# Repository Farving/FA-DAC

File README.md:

# FA-DAC
Farving Acoustic DAC /w FA-Core interface

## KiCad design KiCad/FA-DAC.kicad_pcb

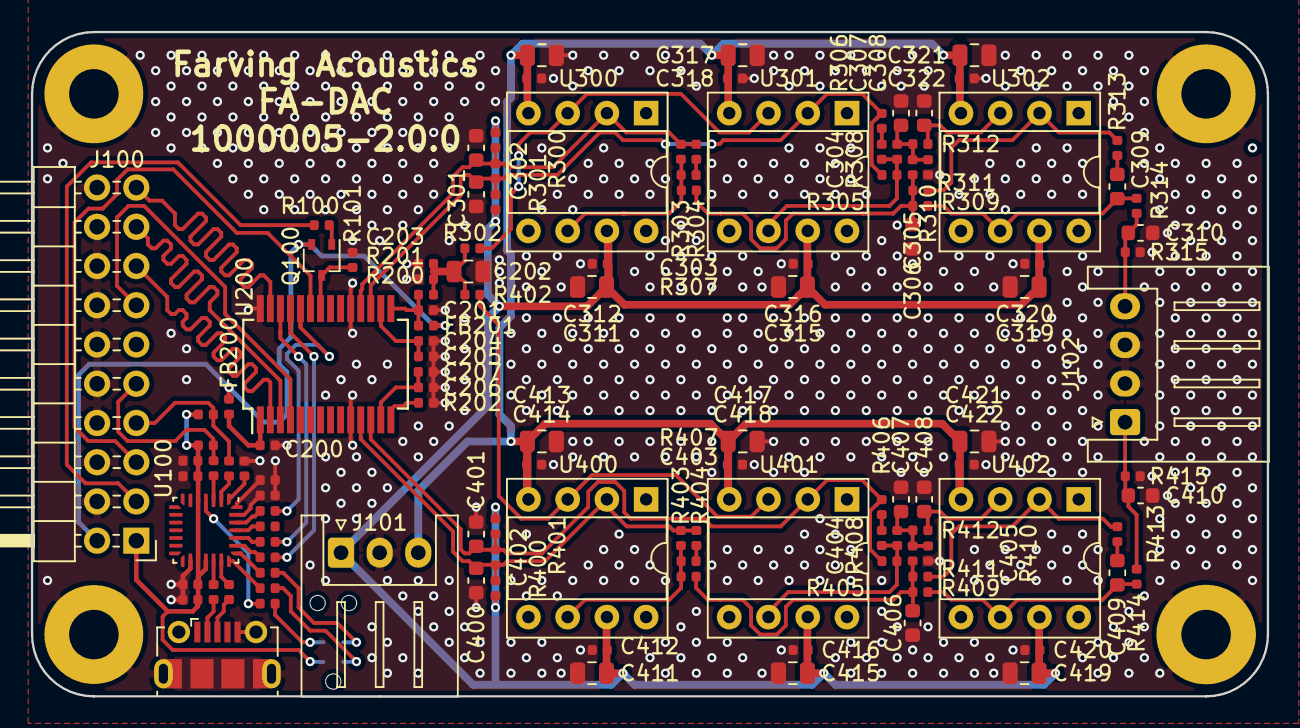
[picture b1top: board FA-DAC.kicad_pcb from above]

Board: 2 copper layers, 80.0 x 43.0 mm, 128 parts (1 on the bottom side), 71 nets.

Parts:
C1: 4.7u; C_0402_1005Metric
C2, C200, C201, C203, C204, C206, C302, C312, C314, C316, C318, C320, C322, C402, C412, C414, C416, C418, C420, C422: 100n; C_0402_1005Metric
C3: 10n; C_0402_1005Metric
C4: 1u; C_0402_1005Metric
C202: 47u; C_0805_2012Metric
C205, C207: 10u; C_0402_1005Metric
C300, C301, C400, C401: 1n; C_0603_1608Metric
C303, C304, C403, C404: 100p; C_0402_1005Metric
C305, C405: 390p; C_0402_1005Metric
C306, C307, C406, C407: 5.6n; C_0603_1608Metric
C308, C309, C408, C409: 2.7n; C_0603_1608Metric
C310, C410: 3.9n; C_0603_1608Metric
C311, C313, C315, C317, C319, C321, C411, C413, C415, C417, C419, C421: 10u; C_0805_2012Metric
FB200, FB201: 600Z; L_0402_1005Metric
J100: Conn_02x10_Odd_Even; PinHeader_2x10_P2.54mm_Horizontal
J101: JST_XH_S3B; JST_XH_S3B-XH-A_1x03_P2.50mm_Horizontal
J102: JST_XH_S4B; JST_XH_S4B-XH-A_1x04_P2.50mm_Horizontal
J103: USB_OTG; USB_Micro-B_Molex-105017-0001
J104: TC2030; Tag-Connect_TC2030-IDC-NL_2x03_P1.27mm_Vertical
PCB100: 70x43; PCB_Board_70x43
Q100: BC856W; SOT-323_SC-70
R1, R2: 2.2k; R_0402_1005Metric
R3, R4, R5, R6, R7, R8, R12, R13, R14, R304, R306, R313, R404, R406, R413: 100R; R_0402_1005Metric
R9, R100, R101: 10k; R_0402_1005Metric
R10, R11, R17, R18: 0R; R_0402_1005Metric
R200: 2.21k; R_0402_1005Metric
R201: 2.8k; R_0402_1005Metric
R202: 2.49k; R_0402_1005Metric
R300, R301, R303, R305, R400, R401, R403, R405: 2k; R_0402_1005Metric
R302, R307, R308, R402, R407, R408: 680R; R_0402_1005Metric
R309, R310, R409, R410: 220R; R_0402_1005Metric
R311, R312, R314, R411, R412, R414: 330R; R_0402_1005Metric
R315, R415: NM; R_0402_1005Metric
U100: STM32F042G4Ux; QFN-28_4x4mm_P0.5mm
U200: AD1955; SSOP-28_5.3x10.2mm_P0.65mm
U300, U301, U302, U400, U401, U402: AD797; DIP-8_W7.62mm_Socket

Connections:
+3V3: C1.1, C2.1, C3.1, C4.1, J100.1, J104.1, R1.1, R2.1, U100.5, U100.17, U100.18
+5V: FB200.1, FB201.1, J100.2, Q100.2
+15V: C311.2, C312.2, C315.2, C316.2, C319.2, C320.2, C411.2, C412.2, C415.2, C416.2, C419.2, C420.2, J101.1, R300.2, R301.1, R400.2, R401.1, U300.7, U301.7, U302.7, U400.7, U401.7, U402.7
-15V: C313.1, C314.1, C317.1, C318.1, C321.1, C322.1, C413.1, C414.1, C417.1, C418.1, C421.1, C422.1, J101.3, U300.4, U301.4, U302.4, U400.4, U401.4, U402.4
/BOOT0: R9.1, U100.1
/DAC/Vbias: C202.1, C203.1, R200.1, R201.1, R302.2, R402.2
/ENABLE: J100.5, U200.23
/I2C_ADDR0: R18.1, U100.28
/I2C_ADDR1: R17.1, U100.27
/I2C_SCL: J100.9, R2.2, R5.2
/I2C_SDA: J100.7, R1.2, R4.2
/I2S_BCLK: J100.17, U200.3
/I2S_LRCLK: J100.15, U200.2
/I2S_MCLK: J100.19, U200.27
/I2S_SD0: J100.13, U200.4
/Left Buffer/InN: C301.1, C302.1, R301.2, R305.2, R306.2, U200.17, U301.2
/Left Buffer/InP: C300.2, C302.2, R300.1, R303.2, R304.2, U200.18, U300.2
/Left Buffer/Out: C310.2, J102.4, R314.1, R315.1
/MUTE: Q100.3, R101.2, U200.22
/NRST: J104.3, R3.2
/Right Buffer/InN: C401.1, C402.1, R401.2, R405.2, R406.2, U200.12, U401.2
/Right Buffer/InP: C400.2, C402.2, R400.1, R403.2, R404.2, U200.11, U400.2
/Right Buffer/Out: C410.2, J102.1, R414.1, R415.1
/SPI_CS: R14.1, U200.25
/SPI_MOSI: R8.2, U200.24
/SPI_SCK: R6.2, U200.26
/SWCLK: J104.4, R13.1
/SWDIO: J104.2, R12.1
/USB_DM: J103.2, R10.1
/USB_DP: J103.3, R11.1
/nMUTE: J100.3, R100.2
GND: C1.2, C2.2, C3.2, C4.2, C200.2, C201.2, C202.2, C203.2, C204.2, C205.2, C206.2, C207.2, C300.1, C301.2, C306.1, C307.2, C308.1, C310.1, C311.1, C312.1, C313.2, C314.2, C315.1, C316.1, C317.2, C318.2, C319.1, C320.1, C321.2, C322.2, C400.1, C401.2, C406.1, C407.2, C408.1, C410.1, C411.1, C412.1, C413.2, C414.2, C415.1, C416.1, C417.2, C418.2, C419.1, C420.1, C421.2, C422.2, J100.4, J100.6, J100.8, J100.10, J100.12, J100.14, J100.16, J100.18, J100.20, J101.2, J102.2, J102.3, J103.5, J103.6, J104.5, PCB100.1, PCB100.2, PCB100.3, PCB100.4, R9.2, R17.2, R18.2, R101.1, R201.2, R202.2, R310.2, R315.2, R410.2, R415.2, U100.16, U200.10, U200.19, U200.28
unnamed: C200.1, FB200.2, U200.1
unnamed: C201.1, FB201.2, R200.2, U200.15
unnamed: C204.1, C205.1, U200.16
unnamed: C206.1, C207.1, U200.13
unnamed: C303.1, R303.1, R307.2, U300.6
unnamed: C303.2, R304.1
unnamed: C304.1, R305.1, R308.2, U301.6
unnamed: C304.2, R306.1
unnamed: C305.1, C307.1, R308.1, R310.1, R312.2
unnamed: C305.2, C306.2, R307.1, R309.2, R311.2
unnamed: C308.2, R312.1, U302.3
unnamed: C309.1, R309.1, R314.2, U302.6
unnamed: C309.2, R313.1
unnamed: C403.1, R403.1, R407.2, U400.6
unnamed: C403.2, R404.1
unnamed: C404.1, R405.1, R408.2, U401.6
unnamed: C404.2, R406.1
unnamed: C405.1, C407.1, R408.1, R410.1, R412.2
unnamed: C405.2, C406.2, R407.1, R409.2, R411.2
unnamed: C408.2, R412.1, U402.3
unnamed: C409.1, R409.1, R414.2, U402.6
unnamed: C409.2, R413.1
unnamed: Q100.1, R100.1
unnamed: R3.1, U100.4
unnamed: R4.1, U100.2
unnamed: R5.1, U100.3
unnamed: R6.1, U100.24
unnamed: R7.1, U100.25
unnamed: R8.1, U100.26
unnamed: R10.2, U100.19
unnamed: R11.2, U100.20
unnamed: R12.2, U100.21
unnamed: R13.2, U100.22
unnamed: R14.2, U100.23
unnamed: R202.1, U200.14
unnamed: R302.1, U300.3, U301.3
unnamed: R311.1, R313.2, U302.2
unnamed: R402.1, U400.3, U401.3
unnamed: R411.1, R413.2, U402.2

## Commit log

2020-03-25 Add AD1955 Schematic
    Add Output buffer
2020-06-30 Progress Commit
2020-11-10 Update for release
